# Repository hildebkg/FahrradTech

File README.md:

# FahrradTech

Senior design project files for FahrradTech: an affordable, feature-rich bike computer with integrated safety accessories.

## Navigation

* [/img](/img): project images (referenced throughout this repo)
* [/main](/main): project source code
* [/managed_components](/managed_components/): project libraries
* [/references](/references/): datasheets, etc
* [/schematics](/schematics/): hardware design files
* [/sim](/sim): hardware simulation files

## Getting Started

This project utilizes the official Espressif Systems IoT Development Framework (ESP-IDF). You can view Espressif's official getting started docs [here](https://docs.espressif.com/projects/esp-idf/en/stable/esp32/get-started/index.html). I did a manual installation on Windows 10 (more info on that specifically [here](https://docs.espressif.com/projects/esp-idf/en/stable/esp32/get-started/windows-setup.html)).

* Download the proper installer for your machine (I used “Universal Online Installer 2.3.4” for Windows 10) and run it.
  * I mostly ran with default settings, but I did check the box to install the IDE in case I ever wanted to use it.
* After installation is complete, open a command prompt and run the following commands:
  * `cd C:\Espressif\frameworks\esp-idf-v5.4` (or whatever your install directory is)
  * `install.bat`
    * This installs the ESP-IDF Python virtual environment.
  * `export.bat`
    * This adds ESP-IDF Tools to PATH (not required).
* Keep things simple and get a demo project from [here](https://github.com/espressif/esp-idf/tree/v5.2.5/examples/get-started) or from your install directory (in \examples\get-started). Copy the entire folder to your desired workspace.
* Download the required serial drivers for your board.
  * My board contains a CP2102 USB to UART bridge, but others may differ. If yours has a CP2102, you can download the drivers from Silicon Labs [here](https://www.silabs.com/developer-tools/usb-to-uart-bridge-vcp-drivers?tab=downloads).
* Connect your ESP32 device to your machine and take note of the port to which it is connected. You will need this for the next step. On Windows, this can be checked via the Device Manager.
* To test your chosen example project, fire up either ESP-IDF Cmd or ESP-IDF PowerShell and run the following commands:
  * `cd <dir_containing_example_project>`
  * `idf.py add-dependency esp32`
    * This adds the Board Support Package (BSP) for ESP32 boards. If you have something specific, you can look for it in the [IDF Component Registry](https://components.espressif.com/).
  * `idf.py build`
    * This builds the project. This will take a bit the first time!
  * `idf.py – p COM# flash`
    * This flashes your device with the most recent build.
    * Make sure to replace "COM#" with the port your device is currently using.
  * `idf.py -p COM# monitor`
    * This relays serial data to and from your target device's serial port. This allows you to see output from your board after it has been flashed.
    * More information [here](https://docs.espressif.com/projects/esp-idf/en/stable/esp32/api-guides/tools/idf-monitor.html).
* To add extra components to your project (from within ESP-IDF CMD or PowerShell):
  * `cd <dir_containing_example_project>`
  * `idf.py add-dependency "component_name"`
    * You should replace "component_name" with the name contained in the [IDF Component Registry](https://components.espressif.com/).
  * `idf.py reconfigure`
    * Processes the `idf_component.yml` file in your `main` folder for each component in your project and resolves dependencies.
    * Creates/updates the `dependencies.lock` file in your  project directory with the full dependency list.
    * Downloads all newly-added depedencies to the `managed_components` folder in your project directory.
* If you want to remove a component you have added, you can simply edit the `/main/idf_component.yml` directly. For example, if you added the `espressif/esp_lcd_st7796` component but no longer want it, you can remove that corresponding line in your YAML file and then run `idf.py reconfigure`. You will get a message similar to "NOTICE: Deleting 1 unused components", and the component will be removed for you. Your `dependencies.lock` file will also be updated.
* If you'd like to make development easier in Visual Studio Code with the C/C++ extension, you should add the following to the "include path" setting for the extension: `C:/Espressif/frameworks/esp-idf-v5.4/components/**` (or whatever your specific path is). This will make it so that VS Code can find standard ESP header files that aren't necessarily in your `managed_components folder`.

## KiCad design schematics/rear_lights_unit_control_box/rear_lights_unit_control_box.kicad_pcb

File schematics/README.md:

# Hardware Design Files

Schematics and PCB layouts for this project were created in KiCad 8.0.

For convenience, you can view a PDF of each schematic below:

* [Bike computer](bike_computer/bike_computer.pdf)
* [Rear lights unit](rear_lights_unit/rear_lights_unit.pdf)
* [Rear lights unit control box](rear_lights_unit_control_box/rear_lights_unit_control_box.pdf)

Other important components:

* [Symbol library file](FahrradTech.kicad_sym)
* [Footprint files](FahrradTech.pretty/)

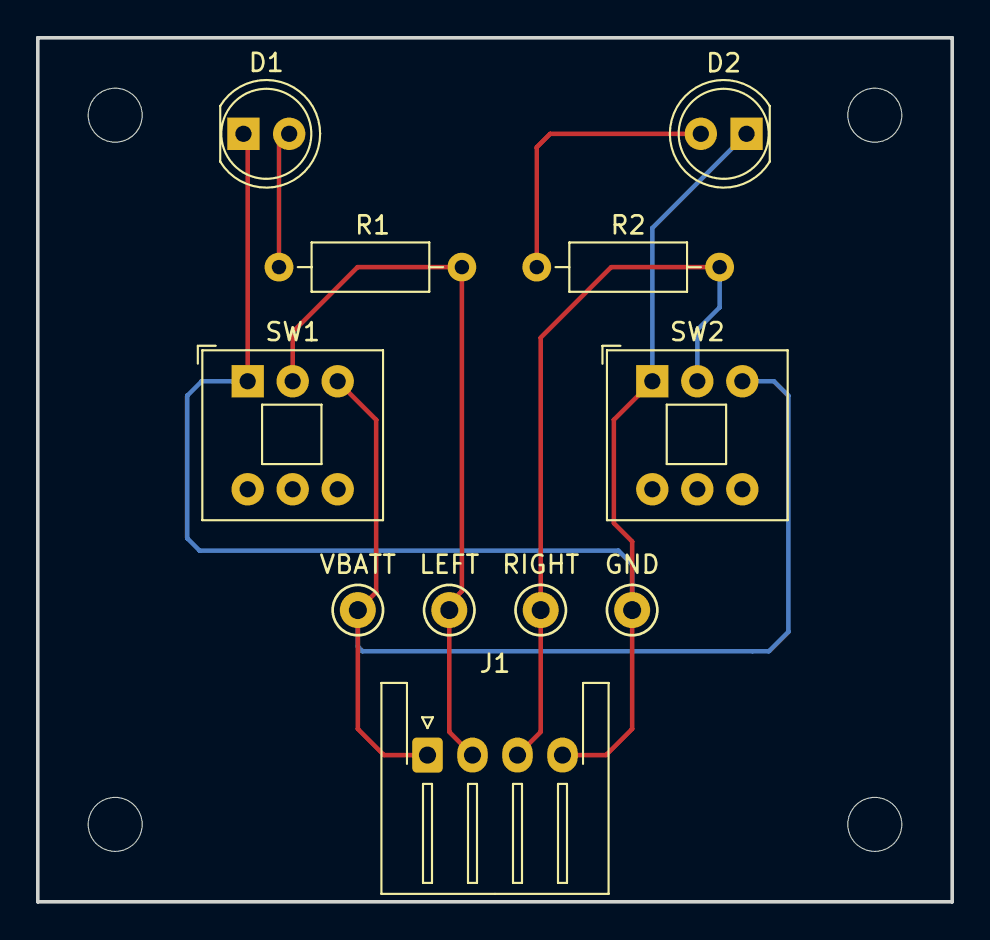
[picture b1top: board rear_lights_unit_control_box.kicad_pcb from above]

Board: 2 copper layers, 50.8 x 48.0 mm, 11 parts (0 on the bottom side), 6 nets.

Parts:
D1, D2: LED; LED_D5.0mm
J1: Conn_01x04_Socket; JST_XH_S4B-XH-A-1_1x04_P2.50mm_Horizontal
R1, R2: 120; R_Axial_DIN0207_L6.3mm_D2.5mm_P10.16mm_Horizontal
SW1, SW2: SW_SPDT; SW_Push_2P2T_Toggle_CK_PVA2xxH2xxxxxxV2
TP1: VBATT; TestPoint_Keystone_5000-5004_Miniature
TP2: LEFT; TestPoint_Keystone_5000-5004_Miniature
TP3: RIGHT; TestPoint_Keystone_5000-5004_Miniature
TP4: GND; TestPoint_Keystone_5000-5004_Miniature

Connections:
GND: D1.1 (K), D2.1 (K), J1.4, SW1.1 (A), SW2.1 (A), TP4.1
LEFT_TURN_EN: J1.2, R1.1, SW1.2 (B), TP2.1
unnamed: D1.2 (A), R1.2
unnamed: D2.2 (A), R2.2
RIGHT_TURN_EN: J1.3, R2.1, SW2.2 (B), TP3.1
V_OUT: J1.1, SW1.3 (C), SW2.3 (C), TP1.1

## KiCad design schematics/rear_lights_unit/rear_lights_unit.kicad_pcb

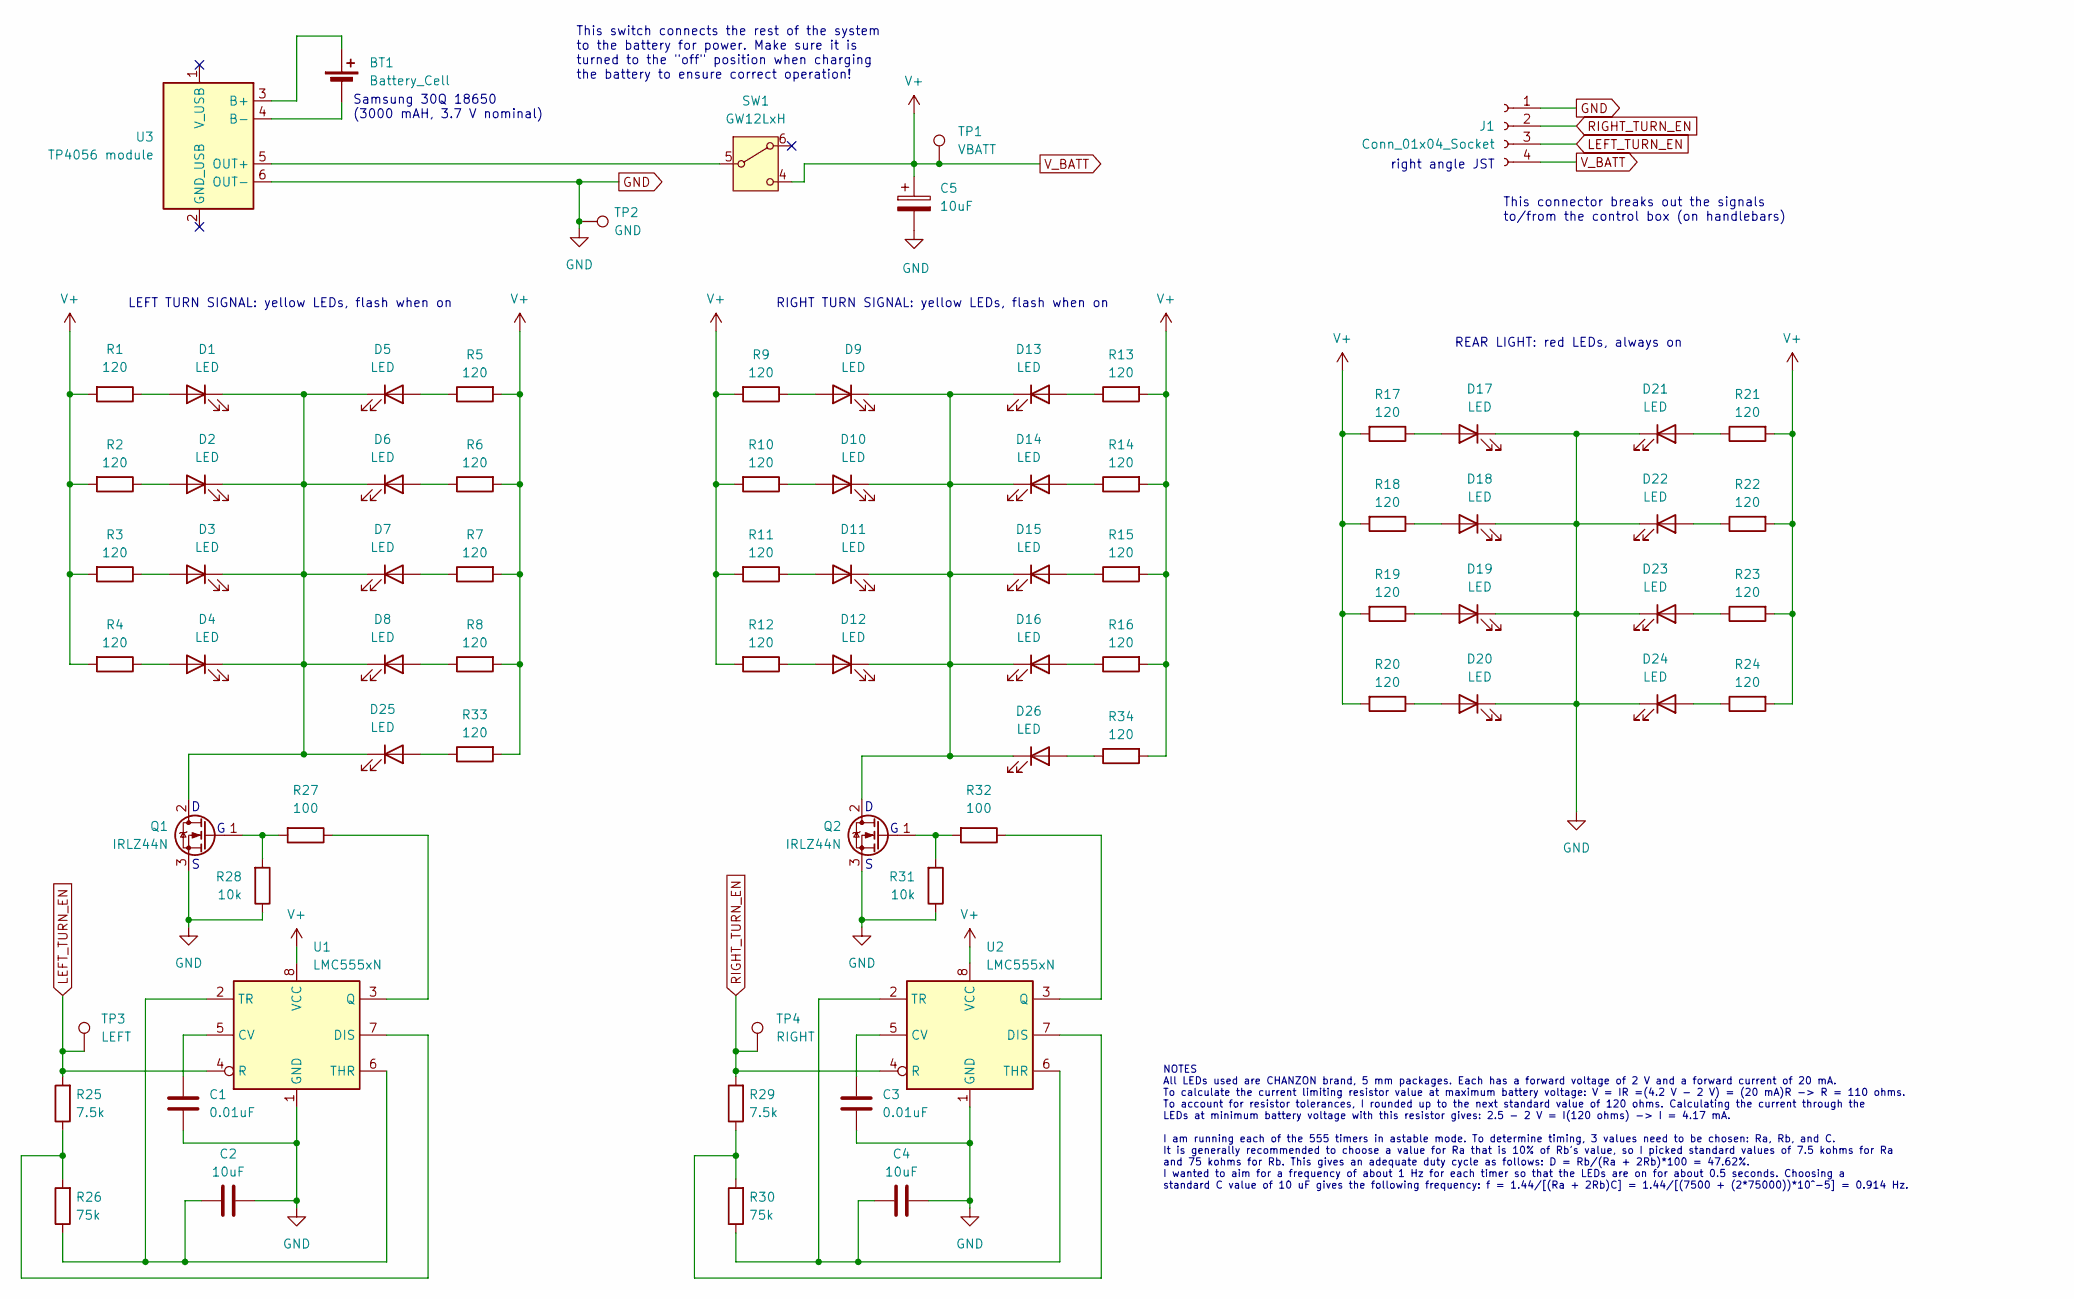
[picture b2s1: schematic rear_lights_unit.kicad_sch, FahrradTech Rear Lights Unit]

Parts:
BT1: Battery_Cell; BatteryHolder_18650; Part Num Samsung 30Q 18650
C1, C3: 0.01uF; C_Rect_L4.6mm_W2.0mm_P2.50mm_MKS02_FKP02; Part Num K103K15X7RF5TK2
C2, C4: 10uF; C_Rect_L4.6mm_W2.0mm_P2.50mm_MKS02_FKP02; Part Num FG18X5R1E106MRT06
C5: 10uF; CP_Radial_D5.0mm_P2.00mm; Part Num ECA-1EM100
D1, D2, D3, D4, D5, D6, D7, D8, D9, D10, D11, D12, D13, D14, D15, D16, D17, D18, D19, D20, D21, D22, D23, D24, D25, D26: LED; LED_D5.0mm; Part Num Chanzon LED
J1: Conn_01x04_Socket; JST_XH_S4B-XH-A_1x04_P2.50mm_Horizontal; Part Num JST XH-2.54
Q1, Q2: IRLZ44N; TO-220-3_Horizontal_TabUpNoHole; Part Num IRLZ44N
R1, R2, R3, R4, R5, R6, R7, R8, R9, R10, R11, R12, R13, R14, R15, R16, R17, R18, R19, R20, R21, R22, R23, R24, R33, R34: 120; R_Axial_DIN0207_L6.3mm_D2.5mm_P10.16mm_Horizontal; Part Num MFR-25SFTF52-120R
R25, R29: 7.5k; R_Axial_DIN0207_L6.3mm_D2.5mm_P10.16mm_Horizontal; Part Num MFR-25FTE52-7K5
R26, R30: 75k; R_Axial_DIN0207_L6.3mm_D2.5mm_P10.16mm_Horizontal; Part Num MFR-25FTE52-75K
R27, R32: 100; R_Axial_DIN0207_L6.3mm_D2.5mm_P10.16mm_Horizontal; Part Num MFR-25SFTF52-100R
R28, R31: 10k; R_Axial_DIN0207_L6.3mm_D2.5mm_P10.16mm_Horizontal; Part Num MFR-25SFRF52-10K
SW1: GW12LxH; SW_Lever_1P2T_NKK_GW12LxH; Part Num GW12LCH
TP1: VBATT; TestPoint_Keystone_5000-5004_Miniature; Part Num Keystone Electronics 5000
TP2: GND; TestPoint_Keystone_5000-5004_Miniature; Part Num Keystone Electronics 5002
TP3: LEFT; TestPoint_Keystone_5000-5004_Miniature; Part Num Keystone Electronics 5001
TP4: RIGHT; TestPoint_Keystone_5000-5004_Miniature; Part Num Keystone Electronics 5001
U1, U2: LMC555xN; DIP-8_W7.62mm; Part Num LMC555CN/NOPB
U3: TP4056 module; TP4056_module; Part Num TP4056 module

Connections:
GND: C1.2, C2.1, C3.2, C4.1, C5.2, D17.1 (K), D18.1 (K), D19.1 (K), D20.1 (K), D21.1 (K), D22.1 (K), D23.1 (K), D24.1 (K), J1.1, Q1.3 (S), Q2.3 (S), R28.1, R31.1, TP2.1, U1.1 (GND), U2.1 (GND), U3.6 (OUT-)
LEFT_TURN_EN: J1.3, R25.2, TP3.1, U1.4 (R)
unnamed: BT1.1 (+), U3.3 (B+)
unnamed: BT1.2 (-), U3.4 (B-)
unnamed: D1.2 (A), R1.1
unnamed: D1.1 (K), D2.1 (K), D3.1 (K), D4.1 (K), D5.1 (K), D6.1 (K), D7.1 (K), D8.1 (K), D25.1 (K), Q1.2 (D)
unnamed: D2.2 (A), R2.1
unnamed: D3.2 (A), R3.1
unnamed: D4.2 (A), R4.1
unnamed: D5.2 (A), R5.1
unnamed: D6.2 (A), R6.1
unnamed: D7.2 (A), R7.1
unnamed: D8.2 (A), R8.1
unnamed: D9.2 (A), R9.1
unnamed: D10.2 (A), R10.1
unnamed: D9.1 (K), D10.1 (K), D11.1 (K), D12.1 (K), D13.1 (K), D14.1 (K), D15.1 (K), D16.1 (K), D26.1 (K), Q2.2 (D)
unnamed: D11.2 (A), R11.1
unnamed: D12.2 (A), R12.1
unnamed: D13.2 (A), R13.1
unnamed: D14.2 (A), R14.1
unnamed: D15.2 (A), R15.1
unnamed: D16.2 (A), R16.1
unnamed: D17.2 (A), R17.1
unnamed: D18.2 (A), R18.1
unnamed: D19.2 (A), R19.1
unnamed: D20.2 (A), R20.1
unnamed: D21.2 (A), R21.1
unnamed: D22.2 (A), R22.1
unnamed: D23.2 (A), R23.1
unnamed: D24.2 (A), R24.1
unnamed: D25.2 (A), R33.1
unnamed: D26.2 (A), R34.1
unnamed: Q1.1 (G), R27.2, R28.2
unnamed: Q2.1 (G), R31.2, R32.2
unnamed: C1.1, U1.5 (CV)
unnamed: R25.1, R26.2, U1.7 (DIS)
unnamed: R27.1, U1.3 (Q)
unnamed: C2.2, R26.1, U1.2 (TR), U1.6 (THR)
unnamed: C3.1, U2.5 (CV)
unnamed: R29.1, R30.2, U2.7 (DIS)
unnamed: R32.1, U2.3 (Q)
unnamed: C4.2, R30.1, U2.2 (TR), U2.6 (THR)
unnamed: SW1.5, U3.5 (OUT+)
RIGHT_TURN_EN: J1.2, R29.2, TP4.1, U2.4 (R)
V_BATT: C5.1, J1.4, R1.2, R2.2, R3.2, R4.2, R5.2, R6.2, R7.2, R8.2, R9.2, R10.2, R11.2, R12.2, R13.2, R14.2, R15.2, R16.2, R17.2, R18.2, R19.2, R20.2, R21.2, R22.2, R23.2, R24.2, R33.2, R34.2, SW1.4, TP1.1, U1.8 (VCC), U2.8 (VCC)

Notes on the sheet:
REAR LIGHT: red LEDs, always on
This connector breaks out the signals to/from the control box (on handlebars)
This switch connects the rest of the system to the battery for power. Make sure it is turned to the "off" position when charging the battery to ensure correct operation!
right angle JST
Samsung 30Q 18650 (3000 mAH, 3.7 V nominal)
LEFT TURN SIGNAL: yellow LEDs, flash when on
RIGHT TURN SIGNAL: yellow LEDs, flash when on
NOTES All LEDs used are CHANZON brand, 5 mm packages. Each has a forward voltage of 2 V and a forward current of 20 mA. To calculate the current limiting resistor value at maximum battery voltage: V = IR =(4.2 V - 2 V) = (20 mA)R -> R = 110 ohms. To account for resistor tolerances, I rounded up to 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

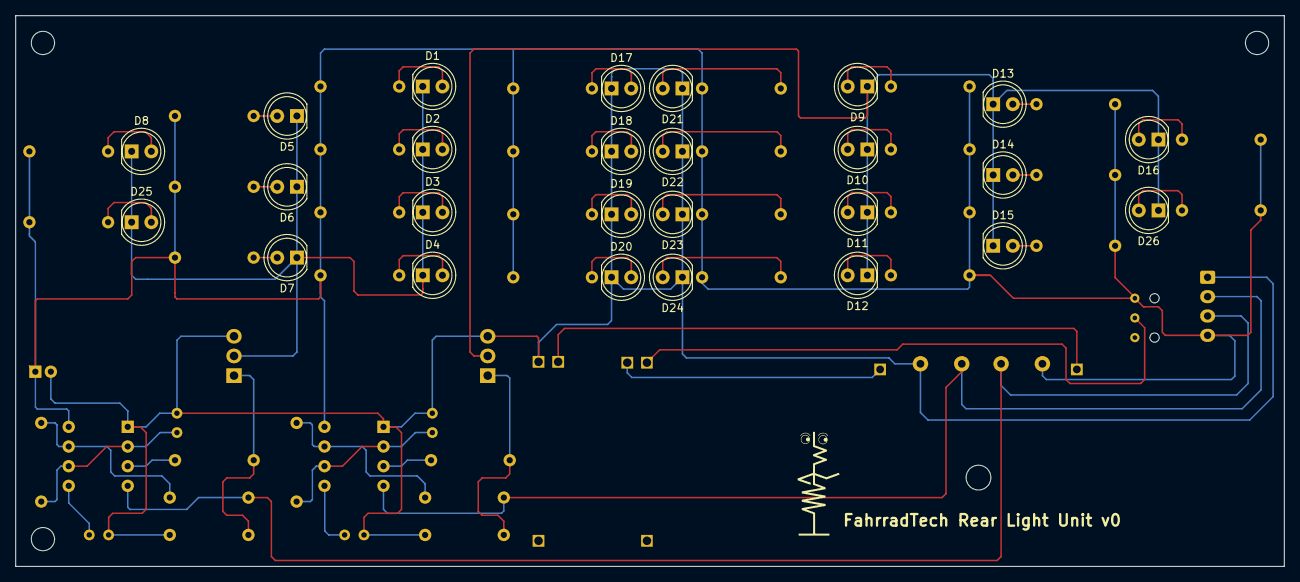
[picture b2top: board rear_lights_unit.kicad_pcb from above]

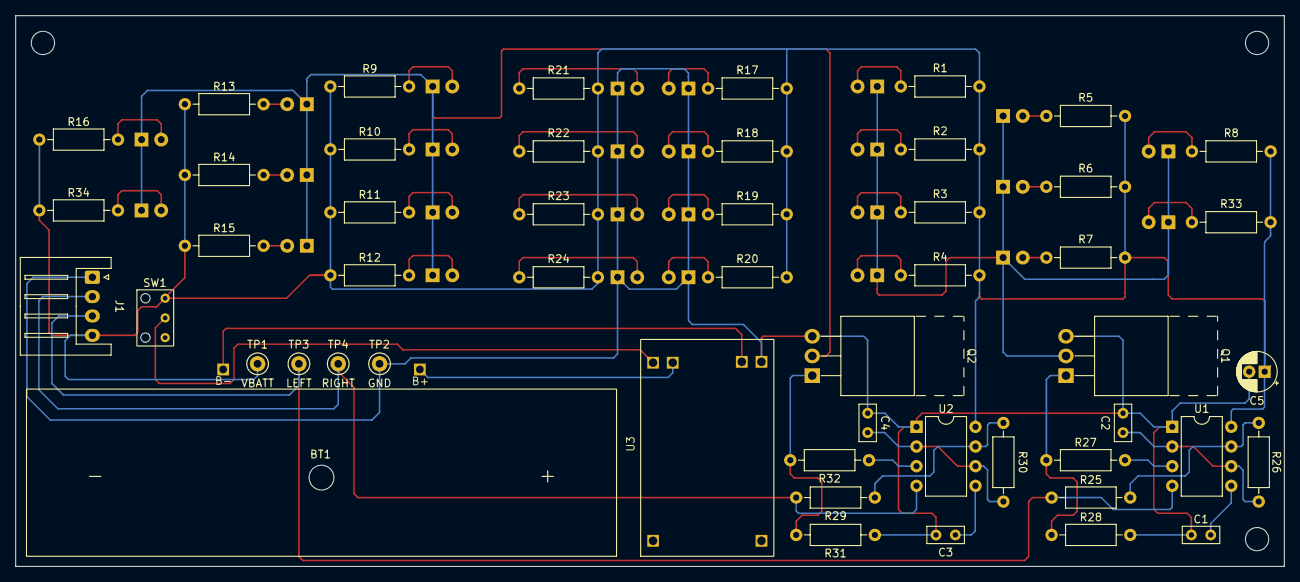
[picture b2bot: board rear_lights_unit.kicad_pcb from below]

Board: 2 copper layers, 163.8 x 71.1 mm, 77 parts (51 on the bottom side), 45 nets.

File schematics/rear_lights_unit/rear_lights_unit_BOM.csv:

"Reference","Value","Part Num","Description","Qty","Footprint"
"BT1","Battery_Cell","Samsung 30Q 18650","18650 battery, 3000 mAH, 3.7 V nominal","1","FahrradTech:BatteryHolder_18650"
"C1,C3","0.01uF","K103K15X7RF5TK2","Unpolarized capacitor, 50 VDC, X7R, 10%, 2.5 mm lead spacing","2","Capacitor_THT:C_Rect_L4.6mm_W2.0mm_P2.50mm_MKS02_FKP02"
"C2,C4","10uF","FG18X5R1E106MRT06 ","Unpolarized capacitor, 25 VDC, X5R, 20%, 5 mm lead spacing","2","Capacitor_THT:C_Rect_L4.6mm_W2.0mm_P2.50mm_MKS02_FKP02"
"C5","10uF","ECA-1EM100","Polarized capacitor, 25 VDC, 20%, 2mm lead spacing","1","Capacitor_THT:CP_Radial_D5.0mm_P2.00mm"
"D1,D2,D3,D4,D5,D6,D7,D8,D9,D10,D11,D12,D13,D14,D15,D16,D17,D18,D19,D20,D21,D22,D23,D24,D25,D26","LED","Chanzon LED","Light emitting diode, red or yellow","26","LED_THT:LED_D5.0mm"
"J1","Conn_01x04_Socket","JST XH-2.54","Generic connector, single row, 01x04, script generated","1","Connector_JST:JST_XH_S4B-XH-A_1x04_P2.50mm_Horizontal"
"Q1,Q2","IRLZ44N","IRLZ44N","47A Id, 55V Vds, 22mOhm Rds Single N-Channel HEXFET Power MOSFET, TO-220AB","2","FahrradTech:TO-220-3_Horizontal_TabUpNoHole"
"R1,R2,R3,R4,R5,R6,R7,R8,R9,R10,R11,R12,R13,R14,R15,R16,R17,R18,R19,R20,R21,R22,R23,R24,R33,R34","120","MFR-25SFTF52-120R ","Resistor, 0.25 W, 1%","26","Resistor_THT:R_Axial_DIN0207_L6.3mm_D2.5mm_P10.16mm_Horizontal"
"R25,R29","7.5k","MFR-25FTE52-7K5 ","Resistor, 0.25 W, 1%","2","Resistor_THT:R_Axial_DIN0207_L6.3mm_D2.5mm_P10.16mm_Horizontal"
"R26,R30","75k","MFR-25FTE52-75K ","Resistor, 0.25 W, 1%","2","Resistor_THT:R_Axial_DIN0207_L6.3mm_D2.5mm_P10.16mm_Horizontal"
"R27,R32","100","MFR-25SFTF52-100R ","Resistor, 0.25 W, 1%","2","Resistor_THT:R_Axial_DIN0207_L6.3mm_D2.5mm_P10.16mm_Horizontal"
"R28,R31","10k","MFR-25SFRF52-10K ","Resistor, 0.25 W, 1%","2","Resistor_THT:R_Axial_DIN0207_L6.3mm_D2.5mm_P10.16mm_Horizontal"
"SW1","GW12LxH","GW12LCH","SPDT paddle switch, red, right-angle","1","FahrradTech:SW_Lever_1P2T_NKK_GW12LxH"
"TP1","VBATT","Keystone Electronics 5000","Test point loop, red","1","FahrradTech:TestPoint_Keystone_5000-5004_Miniature"
"TP2","GND","Keystone Electronics 5002","Test point loop, black","1","FahrradTech:TestPoint_Keystone_5000-5004_Miniature"
"TP3","LEFT","Keystone Electronics 5001","Test point loop, white","1","FahrradTech:TestPoint_Keystone_5000-5004_Miniature"
"TP4","RIGHT","Keystone Electronics 5001","Test point loop, white","1","FahrradTech:TestPoint_Keystone_5000-5004_Miniature"
"U1,U2","LMC555xN","LMC555CN/NOPB ","CMOS Timer, 555 compatible, PDIP-8","2","Package_DIP:DIP-8_W7.62mm"
"U3","TP4056 module","TP4056 module","18650 battery management module","1","FahrradTech:TP4056_module"

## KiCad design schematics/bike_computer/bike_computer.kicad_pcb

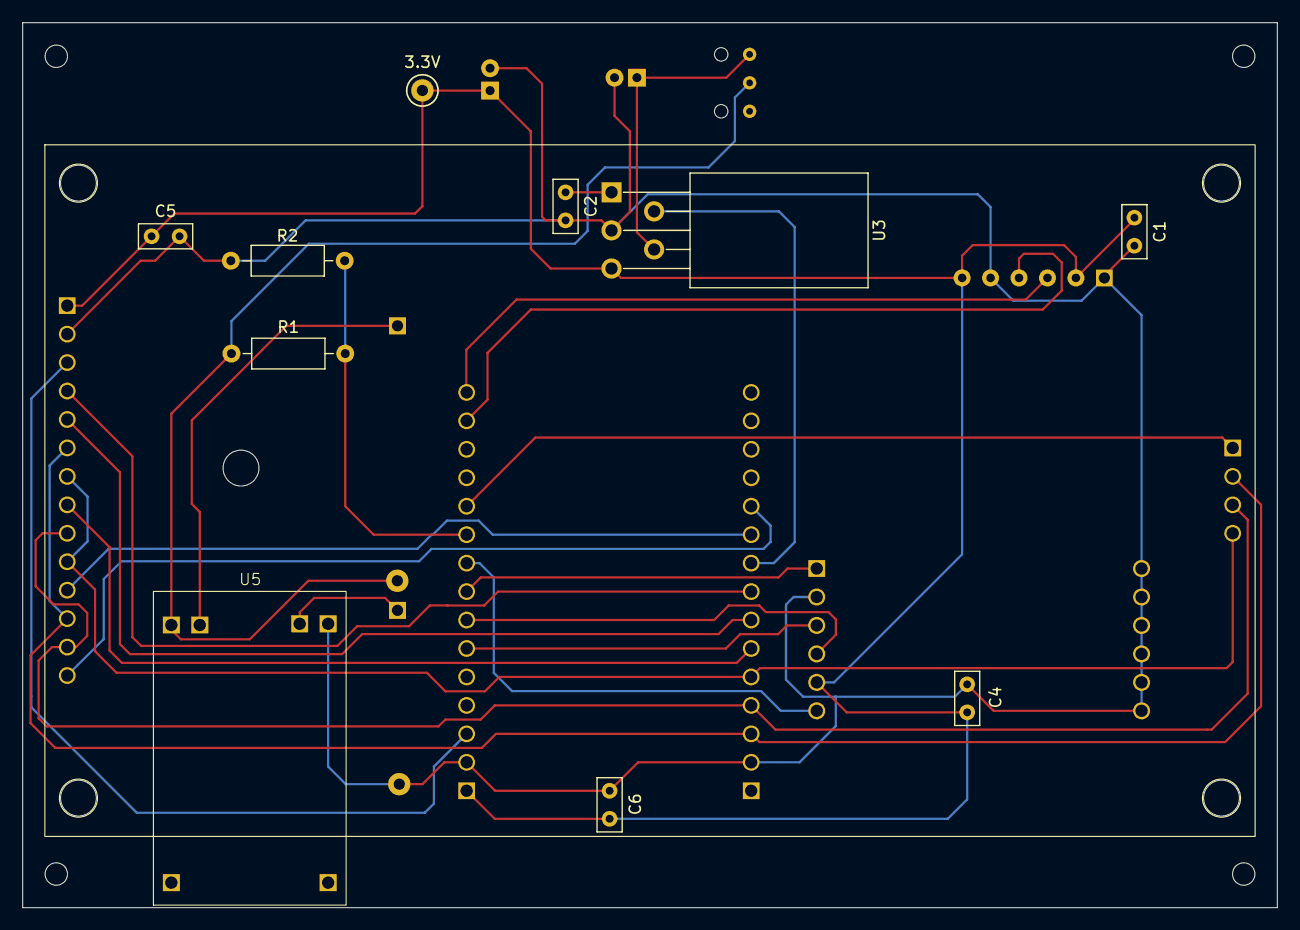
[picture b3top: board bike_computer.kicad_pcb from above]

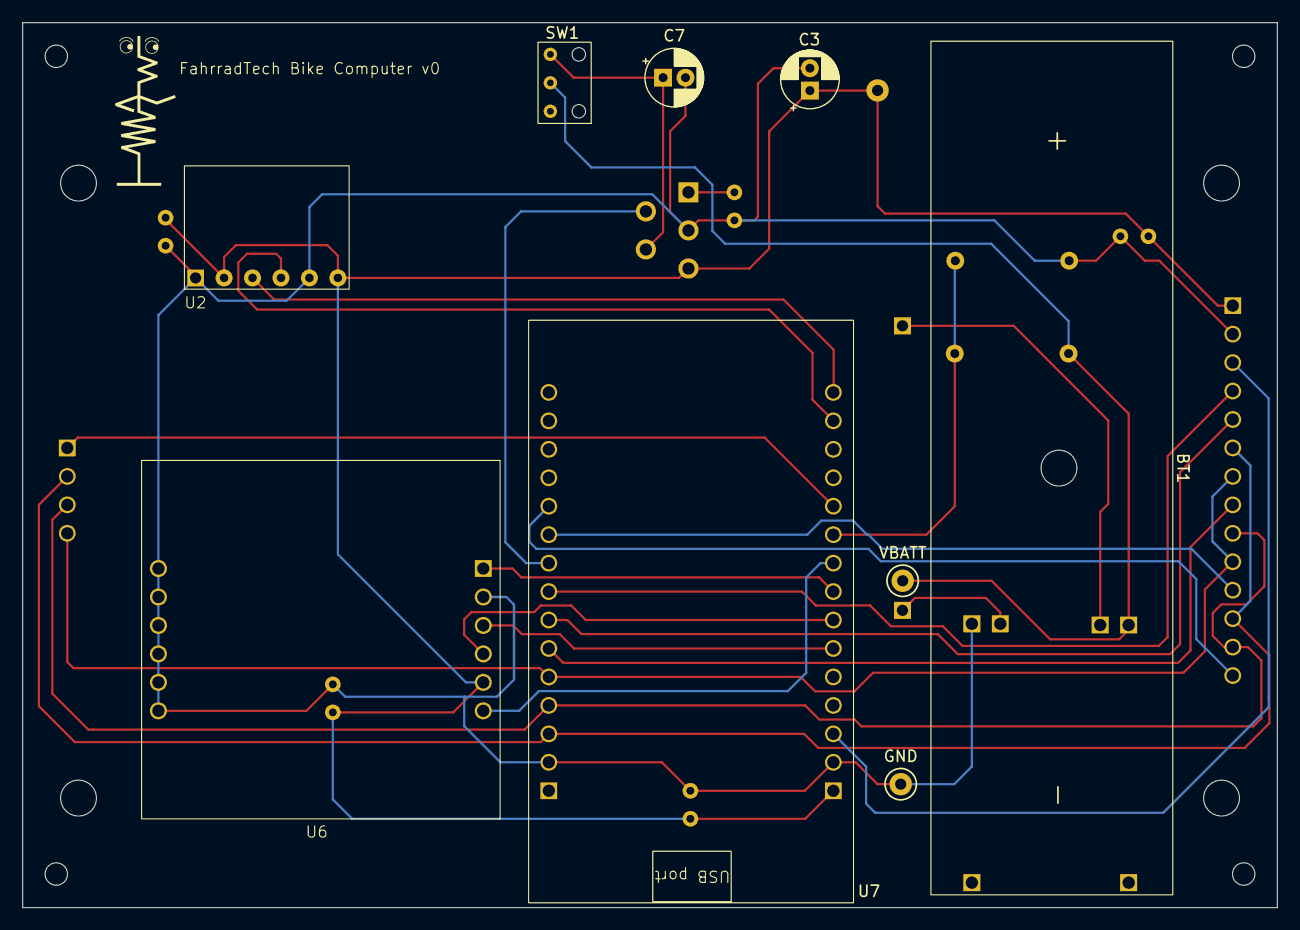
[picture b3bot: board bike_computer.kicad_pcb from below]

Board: 2 copper layers, 112.0 x 79.0 mm, 20 parts (9 on the bottom side), 25 nets.

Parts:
3.3V: 3V3; TestPoint_Keystone_5000-5004_Miniature
BT1: Battery_Cell; BatteryHolder_18650
C1, C4, C5, C6: 0.1uF; C_Rect_L4.6mm_W2.0mm_P2.50mm_MKS02_FKP02
C2: 470pF; C_Rect_L4.6mm_W2.0mm_P2.50mm_MKS02_FKP02
C3, C7: 10uF; CP_Radial_D5.0mm_P2.00mm
GND: GND; TestPoint_Keystone_5000-5004_Miniature
R1: 121k; R_Axial_DIN0207_L6.3mm_D2.5mm_P10.16mm_Horizontal
R2: 40.2k; R_Axial_DIN0207_L6.3mm_D2.5mm_P10.16mm_Horizontal
SW1: GW12LxH; SW_Lever_1P2T_NKK_GW12LxH
U2: BME280; BME280_module
U3: TC1263; TO-220-5_P3.4x3.8mm_StaggerOdd_Lead7.13mm_TabDown
U4: TFT LCD ST7796; Display_420x380
U5: TP4056 module; TP4056_module
U6: RYS352A
U7: ESP-WROOM-32-DevKitV1; ESP-WROOM-32_DevKitV1
VBATT: VBATT; TestPoint_Keystone_5000-5004_Miniature

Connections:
+3.3V: 3.3V.1, C1.1, C3.1, C4.1, C5.1, C6.1, U2.2 (CSB), U2.6 (VDDIO), U3.5 (Vout), U4.1 (VCC), U6.5 (VCC), U7.1 (3V3)
CS: U4.3 (CS), U7.3 (IO15/HSPI_CS0)
GND: C1.2, C2.2, C3.2, C4.2, C5.2, C6.2, C7.2, GND.1, R2.2, U2.1 (GND), U2.5 (SDO), U3.3 (GND), U4.2 (GND), U5.6 (OUT-), U6.2 (GND), U6.7 (GND), U6.8 (GND), U6.9 (GND), U6.10 (GND), U6.11 (GND), U6.12 (GND), U7.2 (GND), U7.29 (GND)
unnamed: BT1.1 (+), U5.3 (B+)
unnamed: BT1.2 (-), U5.4 (B-)
unnamed: U2.4 (SCK), U7.14 (IO22)
unnamed: U2.3 (SDI), U7.15 (IO23)
unnamed: C2.1, U3.1 (BYPASS)
unnamed: C7.1, SW1.6, U3.4 (Vin)
unnamed: U4.5 (DC/RS), U7.24 (IO26)
unnamed: U4.8 (LED), U7.25 (IO27)
unnamed: U4.4 (RESET_N), U7.23 (IO25)
unnamed: U4.7 (SCK), U4.10 (T_CLK), U4.18 (SD_SCK), U7.26 (IO14/HSPI_CLK)
unnamed: U4.6 (SDI(MOSI)), U4.12 (T_DIN), U4.16 (SD_MOSI), U7.28 (IO13/HSPI_ID)
unnamed: U4.9 (SDO(MISO)), U4.13 (T_DO), U4.17 (SD_MISO), U7.27 (IO12/HSPI_Q)
unnamed: U4.11 (T_CS), U7.21 (IO32)
unnamed: U4.14 (T_IRQ_N), U7.20 (IO35)
unnamed: R1.1, SW1.5, U5.5 (OUT+), VBATT.1
unnamed: U6.1 (PPS), U7.8 (IO5)
unnamed: U6.6 (RESET_N), U7.9 (IO18)
unnamed: U6.4 (RXD), U7.7 (IO17/TX2)
unnamed: U6.3 (TXD), U7.6 (IO16/RX2)
unnamed: R1.2, R2.1, U7.10 (IO19)
SD_CS: U4.15 (SD_CS), U7.11 (IO21)
nSHDN: U3.2 (nSHDN), U7.22 (IO33)

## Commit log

2024-11-25 init commit - quick demo project for ESP IDF usage + empty KiCad projects for hardware designs
2024-11-25 added references folder with data sheets, user guides, etc
2024-12-01 replaced SHT3x datasheet with newer version
2024-12-04 added references for the LCD module and LEDs
2025-01-07 did some cleanup and added a gitignore file
2025-01-18 cleanup & gitignore updates for KiCad files
2025-03-18 updated references, created simulation folder
2025-03-18 schematic updates for bike computer, rear light unit, rear light unit control box
2025-03-23 migrated project to use pure esp-idf tools (no PlatformIO), added demo file for sht3x sensor, updated main readme
2025-03-23 quick main readme fix, added a readme file to the rest of the subdirectories that didn't have one already
2025-03-23 added BMP280 pressure sensor demo draft
2025-03-23 more schematic updates
2025-03-24 adding the managed_components folder to the repo so that I can track my own changes to them
2025-03-24 modified debugging messages, fixed bugs in the way pressure and altitude were calculated, removed unused humidity measurement function
2025-03-24 finalized bmp280 demo code
2025-03-24 forgot to commit .gitignore changes (stop ignoring /managed_components)
2025-03-24 modified READMEs to help explain managed_components folder
2025-03-24 fixed relative link issue in READMEs (skull emoji)
2025-03-25 added new component: espressif\BME280
2025-03-25 made changes to espressif/bme280 component (described in file), added bme280 demo program, made small change to bmp280 demo program to keep output formatting consistent across demos
2025-03-25 added folder for storing screenshots and other images related to the project
2025-03-26 finalized rear light unit schematic, added corresponding BOM
2025-03-26 finalized rear light unit control box schematic, added corresponding BOM
2025-03-27 rear light control box: added test points to I/O signals, improved BOM (added specific part numbers, descriptions, etc), started PCB layout. started project footprint file, fixed error in TP4056 symb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
2025-03-27 rear light unit control box: finished first draft of PCB
2025-03-28 fixed page size for rear light control box PCB so I can print to scale, regenerated related files
2025-03-28 rear light unit: finished first draft of PCB, regenerated all related files
2025-03-28 added more datasheets/other references, started img folder for screenshots and whatnot
2025-03-29 completed footprint for LCD breakout board
2025-03-30 added footprint for RYS352A GNSS module
2025-03-31 modified TP4056 dimensions, fixed typo in footprint file name
2025-03-31 cleaned up managed_components folder and specified which sensors are not actually being used
2025-03-31 added footprint for BME280 module, made some small changes to LCD and GNSS module symbols
2025-03-31 added new footprint and symbol for my ESP32 dev module (previous ones were for a slightly different module)
2025-03-31 more schematic updates: re-did bike computer with better ESP32 symbol, fixed component data on other schematics (somehow some of the part nums, descriptions, etc disappeared??)
2025-03-31 added more dev env details to main readme, added symbol/footprint for power switch and 5-pin TO-220
2025-04-01 rear light unit control box PCB finalized!
2025-04-01 finalized rear light unit v0
2025-04-04 fixed naming typo, added 3D models for TP4056, ESP32, and BME280 modules
2025-04-04 bike computer layout v0
2025-04-04 updated both sets of light unit board files to include the newly-added 3D models
